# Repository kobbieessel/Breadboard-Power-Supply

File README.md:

# Breadboard Power Supply Module 

A compact, dual-output breadboard power supply that delivers **regulated 5V and 3.3V** from a 12V DC input. Designed for electronics prototyping, embedded systems, and educational projects.

## Overview

This custom PCB module is designed to fit alongside a standard breadboard and provide clean, stable power rails via male headers and screw terminals. The module uses **LM7805** and **LM317** linear regulators, along with standard passive components, to output 5V and 3.3V from a single 12V barrel jack input.

Ideal for powering:
- Microcontrollers (Arduino, ESP32, etc.)
- Sensors and modules
- Digital/analog circuits
- Educational breadboard projects

---
## Breadboard Power Supply Images
### Top View

### Bottom View

### Front View

### Schematic Capture

### PCB Layout

---

## Specifications

| Feature                | Description                             |
|------------------------|-----------------------------------------|
| **Input Voltage**      | 12V DC (Barrel Jack)                    |
| **Output Voltages**    | 5V (LM7805), 3.3V (LM317)               |
| **Current Output**     | Up to 1A (with heatsinks)               |
| **LED Indicator**      | Red LED (power-on status)               |
| **Switch**             | EG1218 toggle switch                    |
| **Connectors**         | Screw terminals & 2.54mm pin headers    |
| **Capacitors**         | 10µF, 0.1µF, and 1µF for decoupling     |
| **PCB Type**           | 2-layer, through-hole design            |
| **Breadboard Ready**   | Outputs connect directly to breadboard  |

---

## Components Used

- **LM7805** – 5V linear voltage regulator
- **LM317** – Adjustable linear regulator (configured for 3.3V)
- **Capacitors** – 10µF, 0.1µF, 1µF
- **Resistors** – 330Ω, 560Ω
- **LED** – Power indicator
- **EG1218 switch** – On/off control
- **DC Barrel Jack** – Power input
- **Pin Headers & Screw Terminals**

---

## Files Included

- `BPS_Schematic_Capture.png` – Circuit schematic
- `BPS_Topview1.png` – 3D top view of the PCB
- `BPS_Bottomview.png` – 3D bottom view of the PCB
- `KiCad/` – Source files for schematic and PCB layout (optional)
- `Gerber/` – Gerber files for fabrication (optional)

---

## Getting Started

1. Connect a **12V DC adapter** to the barrel jack.
2. Toggle the switch to power on the board.
3. Use the screw terminals or headers to connect **3.3V and 5V** rails to your breadboard.
4. Observe the LED indicator for power status.

>  For currents approaching 1A, heatsinks are recommended on the regulators.

---

## Skills Demonstrated

- Circuit design and voltage regulation  
- Component selection and schematic capture (KiCad)  
- Footprint assignment and ERC/DRC validation  
- PCB layout, teardrop optimization, and routing  
- 3D modeling and design review  
- Design for manufacturability (DFM)

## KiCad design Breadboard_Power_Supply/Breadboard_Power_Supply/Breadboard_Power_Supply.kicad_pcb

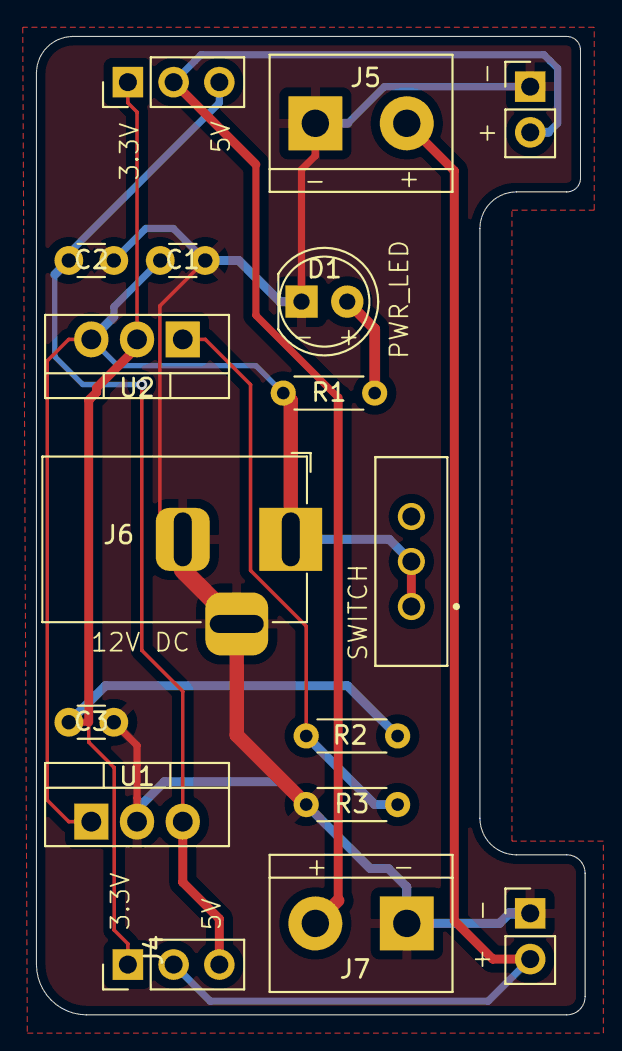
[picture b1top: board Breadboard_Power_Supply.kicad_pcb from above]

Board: 2 copper layers, 30.5 x 54.4 mm, 17 parts (0 on the bottom side), 8 nets.

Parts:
C1: 10u; C_Disc_D3.0mm_W1.6mm_P2.50mm
C2: 0.1u; C_Disc_D3.0mm_W1.6mm_P2.50mm
C3: 1u; C_Disc_D3.0mm_W1.6mm_P2.50mm
D1: LED; LED_D5.0mm
J1, J2: Conn_01x02_Pin; PinHeader_1x02_P2.54mm_Vertical
J3, J4: Conn_01x03_Pin; PinHeader_1x03_P2.54mm_Vertical
J5, J7: Screw_Terminal_01x02; TerminalBlock_bornier-2_P5.08mm
J6: DC_IN; BarrelJack_Horizontal
R1, R2: 330; R_Axial_DIN0204_L3.6mm_D1.6mm_P5.08mm_Horizontal
R3: 560; R_Axial_DIN0204_L3.6mm_D1.6mm_P5.08mm_Horizontal
S1: EG1218; SW_EG1218
U1: LM7805_TO220; TO-220-3_Vertical
U2: LM317_TO-220; TO-220-3_Vertical

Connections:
3.3V: C3.1, J3.1, J4.1, R2.2, U2.2 (VO)
5V: C2.1, J3.3, J4.3, U1.3 (VO)
12V: C1.1, J6.1, R1.2, S1.1, S1.2, U1.1 (VI), U2.3 (VI)
GND: C1.2, C2.2, C3.2, D1.1 (K), J1.1, J2.1, J5.1, J6.2, J6.3, J7.1, R3.1, U1.2 (GND)
unnamed: D1.2 (A), R1.1
unnamed: J1.2, J3.2, J7.2
unnamed: J2.2, J4.2, J5.2
unnamed: R2.1, R3.2, U2.1 (ADJ)

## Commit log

2025-07-16 demo
